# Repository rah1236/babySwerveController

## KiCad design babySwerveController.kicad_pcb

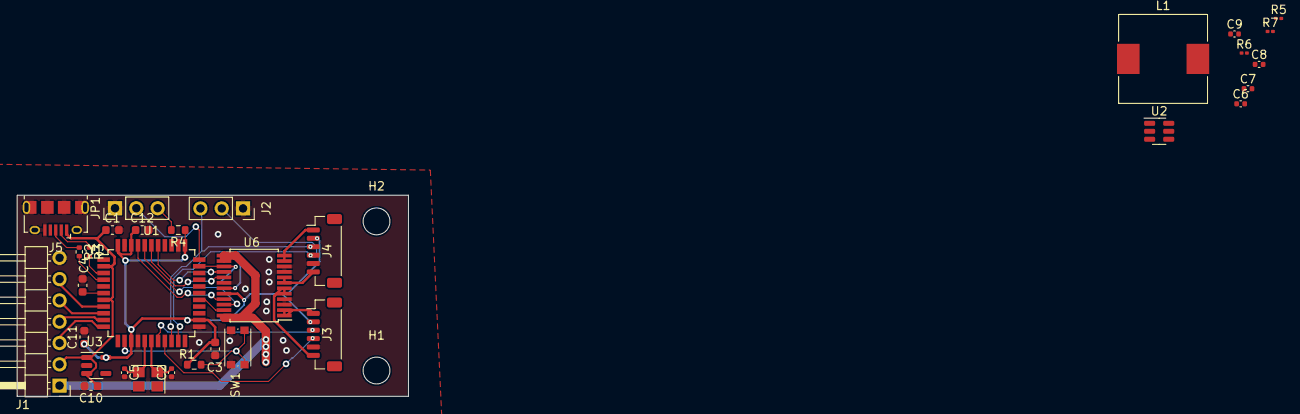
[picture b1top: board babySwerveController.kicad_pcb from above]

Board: 2 copper layers, 46.6 x 24.0 mm, 34 parts (0 on the bottom side), 37 nets.

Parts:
C1, C4, C10, C11: 1uF; C_0603_1608Metric
C2, C5: 22pF; C_0402_1005Metric
C3, C12: 10uF; C_0603_1608Metric
C6: 1uF; C_0402_1005Metric
C7, C8, C9: 22uF; C_0402_1005Metric
H1, H2: MountingHole; MountingHole_3.2mm_M3
J1: Conn_01x07_Female; PinHeader_1x07_P2.54mm_Horizontal
J2: pgm; PinSocket_1x03_P2.54mm_Vertical
J3, J4: Conn_01x06_Male; JST_SH_BM06B-SRSS-TB_1x06-1MP_P1.00mm_Vertical
J5: USB_B_Micro; USB_Micro-B_Amphenol_10118194_Horizontal
JP1: Jumper; PinHeader_1x03_P2.54mm_Vertical
L1: 11uH; L_10.4x10.4_H4.8
R1, R4: 10k; R_0603_1608Metric
R2, R3: 22; R_0402_1005Metric
R5: 200k; R_0201_0603Metric
R6: 100k; R_0201_0603Metric
R7: 18.7k; R_0201_0603Metric
SW1: sw; SW_Push_1P1T_NO_CK_KMR2
U1: ATmega32U4-A; TQFP-44_10x10mm_P0.8mm
U2: MT1470; SOT-23-6
U3: TLV75533PDBV; SOT-23-5
U6: TB6612FNG; SSOP-24_5.3x8.2mm_P0.65mm
Y1: Crystal; Crystal_SMD_TXC_7M-4Pin_3.2x2.5mm

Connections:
+3.3V: C3.1, C11.1, C12.1, J3.2, J4.2, R1.2, R4.1, U1.14 (VCC), U1.24 (AVCC), U1.34 (VCC), U1.42 (AREF), U1.44 (AVCC), U3.5 (OUT), U6.20 (VCC)
+3V3: C8.1, C9.1, L1.2, R6.1
+5V: C1.1, C10.1, J1.2, J5.1 (VBUS), U1.2 (UVCC), U1.7 (VBUS), U3.1 (IN), U3.3 (EN)
/AIN1: U1.41 (PF0), U6.21 (AIN1)
/AIN2: U1.40 (PF1), U6.22 (AIN2)
/BIN1: U1.39 (PF4), U6.17 (BIN1)
/BIN2: U1.38 (PF5), U6.16 (BIN2)
/PWM1H: U1.27 (PD7), U6.23 (PWMA)
/PWM2H: U1.32 (PC7), U6.15 (PWMB)
/SPI_MISO: J1.3, U1.11 (PB3)
/SPI_MOSI: J1.4, U1.10 (PB2)
/SPI_NSS: J1.6, U1.8 (PB0)
/SPI_SCLK: J1.5, U1.9 (PB1)
/UART_RX: J2.2, J4.4, U1.21 (PD3)
/UART_TX: J2.3, J4.3, U1.20 (PD2)
/VBATT: C7.1, J1.1, R5.2, U2.3 (VIN), U6.13 (VM2), U6.14 (VM3), U6.24 (VM1)
/motorA1: J3.1, U6.1 (AO1), U6.2 (AO1)
/motorA2: J4.1, U6.11 (BO1), U6.12 (BO1)
/motorB1: J3.6, U6.5 (AO2), U6.6 (AO2)
/motorB2: J4.6, U6.7 (BO2), U6.8 (BO2)
/qEncoderA1: J3.3, U1.18 (PD0)
/qEncoderB1: J3.4, U1.19 (PD1)
GND: C1.2, C2.1, C3.2, C4.2, C5.2, C7.2, C8.2, C9.2, C10.2, C11.2, C12.2, J1.7, J2.1, J3.5, J4.5, J5.5 (GND), J5.6 (Shield), JP1.1 (A), R7.2, SW1.2, U1.5 (UGND), U1.15 (GND), U1.23 (GND), U1.35 (GND), U1.43 (GND), U2.1 (GND), U3.2 (GND), U6.3 (PGND1), U6.4 (PGND1), U6.9 (PGND2), U6.10 (PGND2), U6.18 (GND)
unnamed: C2.2, U1.17 (XTAL1), Y1.1
unnamed: C4.1, U1.6 (UCAP)
unnamed: C5.1, U1.16 (XTAL2), Y1.2
unnamed: C6.1, L1.1, U2.2 (SW)
unnamed: C6.2, U2.6 (BS)
unnamed: J5.2 (D-), R3.1
unnamed: J5.3 (D+), R2.1
unnamed: JP1.2 (C), U1.33 (~HWB/PE2)
unnamed: JP1.3 (B), R4.2
unnamed: R1.1, SW1.1, U1.13 (~RESET)
unnamed: R2.2, U1.4 (D+)
unnamed: R3.2, U1.3 (D-)
unnamed: R5.1, U2.5 (EN)
unnamed: R6.2, R7.1, U2.4 (FB)

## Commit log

2022-11-13 Atmega32u4 rev
